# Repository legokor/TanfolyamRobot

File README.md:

# LEGO Kör - TanfolyamRobot

## Fejlesztő környezet

Korábban az STMicroelectronics által biztosított `STM32CubeIDE`-t használtuk a firmware fejlesztéséhez, azonban ez egy elég nehézkes és lassú eszköz. Ezért a tanfolyam során áttérünk egy könnyebben használható és gyorsabb parancssoros toolchain-re, az `STM32CubeCLT`-re. Ezt a toolchain-t a Visual Studio Code nevű (továbbiakban `VSCode`) kód szerkesztővel fogjuk használni, így a teljes fejlesztés (fordítás, feltöltés) nagyon könnyen indítható lesz néhány előre beállított `task`-kal.

## Toolchain

Az előző fejezetben említett módon a firmware fejlesztéséhez az STMicroelectronics parancsoros eszközeit használjuk. Sajnos ezek letöltése regisztrációhoz kötött, ezért feltöltöttük a telepítő fájlokat [a körös drive-ra](https://drive.google.com/drive/folders/1nJ2nfvr9kbIkVAWmcgEXpbxK1OUlX8sQ?usp=sharing), így regisztráció nélkül is telepíteni tudjátok - persze teljesen megértjük, ha nem akartok random drive-os fájlokat telepíteni, viszont ez esetben muszáj regisztrálnotok az [STMicroelectronics weboldalán](https://www.st.com/en/development-tools/stm32cubeclt.html), és onnan letölteni.

Letöltés után a telepítő fájlt futtatva telepítsétek a `STM32CubeCLT`-t egy kényelmes helyre, például `C:\STM32CubeCLT`-be.

**FONTOS:** az `STM32CubeCLT` telepítése után újra kell indítani a `VSCode`-ot amennyiben az már meg volt nyitva, különben a `VSCode` nem fogja látni a telepített toolchain-t. Ezen felül Linux rendszerek esetében előfordulhat, hogy a gépet is újra kell indítani, hogy a megfelelő környezeti változók beálljanak.

Jelenleg Windows 10/11-en és Ubuntu-n teszteljük a szoftvert. Más (Linux alapú) platformokon is valószínűleg működni fog - de ezt nem tudjuk garantálni.

## Robot illesztőszoftver

A robotra a firmware letöltése virtuális soros porton történik, a roboton az USB csatlakozó egy `FT232RL` chiphez kapcsolódik.

Előfordulhat Windows esetében, hogy az nem telepíti automatikusan a virtuális soros port driverét. Erre az esetre a fentebbi drive linken elérhető Windows zip-ben találtok egy plusz driver telepítőt, de amúgy ezt is le tudjátok tölteni az [FTDI weboldaláról](https://ftdichip.com/wp-content/uploads/2021/08/CDM212364_Setup.zip), majd pedig kibontani és telepíteni.

## Kiinduló projekt letöltése, megnyitása

A kiinduló projektet a [GitHub repojából](https://github.com/legokor/TanfolyamRobot) tudjuk letölteni, ehhez az oldal megnyitása után jobb oldalt a `Releases` fül alatt kell kiválasztanunk a **legújabb kiadást**, majd a `tanfrobot.zip` fájlra kell kattintani.

A letöltött fájlt helyezzük el egy kényelmes helyre, például `Documents/Lego_Tanfolyam` mappába, majd bontsuk ki. A kibontás után nyissuk meg a `VSCode`-ot, és a `File -> Open Folder...` menüponttal nyissuk meg a kibontott `firmware` mappát (mely többek közt az `Application`, `Drivers`, `Tools` könyvtárakat tartalmazza).

*Extra tipp:* a `VSCode`-ban érdemes telepíteni az `ms-vscode.cpptools` nevű bővítményt, mely C/C++ nyelv támogatást ad a szerkesztőhöz, így például szintaxis kiemelést és automatikus kiegészítést biztosít.

--------------------------------------------

--------------------------------------------

## *Csak a tanfolyamon kell:* projekt áttekintése, build és upload

Az imént megnyitott projektünk fájljait az IDE bal oldalán láthatjuk. A kód számunkra lényegi része a `tanfolyamrobot/Application/src/app.c` fájl lesz. Itt kell majd megoldanunk a tanfolyam során a feladatokat. Az itt található `app_main()` függvény gombnyomásra indul. Ha ebből a függvényből visszatér a programunk, akkor a robot leáll és a kijelzőn megjeleníti a visszatérési értéket.

A kód fordításához és a robotra való feltöltéséhez a `VSCode`-ban előre beállítottunk néhány `task`-ot, melyeket a `CTRL+SHIFT+B` billentyűkombinációval tudtok elindítani. E billentyűkombináció megnyomása után egy legördülő menüből választhatjátok ki, hogy mit szeretnétek csinálni - számunkra a `CMake Build` és az `STM32 Flash Firmware (FTDI)` lesz a fontos. Előbbi lefordítja a kódot, utóbbi pedig feltölti a robotra. A kiválasztás után egy újabb kérdés fog megjelenni, hogy melyik konfigurációt szeretnénk használni - válasszuk a `Release`-t, majd nyomjunk egy entert.

**FONTOS:** a `CMake Build`-et mindig futtassátok le a `STM32 Flash Firmware (FTDI)` előtt, különben a régi kód fog futni a roboton, nem pedig a legutóbb módosított verzió.

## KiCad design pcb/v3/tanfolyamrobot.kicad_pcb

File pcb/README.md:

# TanfolyamRobot - PCB design considerations

_Note: schematic net and pin names are formatted like_ `this`.

## Microcontroller

The main MCU is an [STM32F103C8T6](https://www.st.com/resource/en/datasheet/stm32f103c8.pdf) in LQFP64 package. There's an option to add an ESP8266 module which communicates with the main MCU via UART.

**The full STM32 pinout and pin assignments can be found in [STM32F103_pin_assignment.xls](STM32F103_pin_assignment.xls)**

### Programming

The STM32 can be programmed using the Serial Wire Debug interface or the integrated Device Firmware Updater. The F103's DFU only supports USART1, so that's connected to an FTDI FT232RL USB-UART converter.

In order to use the DFU, the MCU must be booted in System memory mode by pulling the `BOOT0` pin high at reset.
`BOOT0` is controlled by:
 * the FTDI chip's `RSTN` reset signal, which is high when USB is connected.
 * an FTDI output pin controlled by PC software. The pin can be selected by solder jumpers.

### Reset

Both controllers are connected to the same reset signal, which is a combination of the following reset sources:
 * The reset button
 * Debugger port
 * USB 5V connection
 * an FTDI output pin controlled by PC software. The pin can be selected by solder jumpers.

## Power supply

The battery input connects through a polarity protection MOSFET to the `VCC` rail, which drives the motors and the 5V regulator. Therefore the battery voltage must be at least 5V + the regulator's dropout voltage, and can be as high as the motors' and the motor driver's maximum operating voltage. The polarity protection MOSFET's absolute maximum V<sub>GS</sub> and V<sub>DS</sub> must be higher than the supply voltage.

The `+5V` rail powers the FTDI chip, LCD, ultrasonic sensor, motor encoders, and the servo motor. Therefore the ultrasonic sensor and motor encoder outputs shall be connected to a 5V tolerant MCU pin or level-shifted to 3.3V.

The `+3V3` rail powers the rest of the system: STM32, ESP, color sensor, and it's also the `VCCIO` supply of the FTDI chip.

## Motors

The two motors are driven by a DRV8833 module. For maximum flexibility all of its input ports shall be connected to PWM cabable MCU pins, preferably using the same timer. The driver indicates overcurrent/overheat faults on the `FAULTN` pin, and the whole module can be enabled/disabled by the `SLEEPN` pin.

The STM32's timers have a built-in encoder pulse counter module, which uses the CH1-CH2 channel pair. The motors' encoder pins therefore shall be connected to these timer channels.

The servo output has a 3 pin header with 5V supply and a PWM pin.

## Sensors, LCD

The TCS3200 color sensor has a frequency output. 2 config pins activate the RGB color filters, and 2 config pins set the output frequency scaling. The output pin should be connected to a timer of the MCU. The timer's frequency is not critical as the output full scale frequency can be configured between 12 and 600 kHz.

The generic ultrasonic sensor has a trigger and an echo pin. `ECHO` shall be connected to an interrupt-capable MCU pin.

The character LCD screen operates in 4 bit mode. In this configuration only the `D4`-`D7`, `EN` and `RST` pins are used. Contrast can be set by a trimmer potentiometer on the board. The backlight is also controlled by the MCU, but the control signal is pulled up, so it's on by default.

# MCU connection requirement summary

_I know this looks terrible, but it's my only workaround for GitHub's alternating row colors :disappointed:_

| Component     | Pin/Schematic net      | Type             | MCU requiurement                              |
|---------------|------------------------|------------------|-----------------------------------------------|
| DRV8833       | `IN1`, `IN2`           | PWM/fix input    | 1 PWM, 1 PWM/fix, same timer for all channels |
|||||
|               | `IN3`, `IN4`           | PWM/fix input    | 1 PWM, 1 PWM/fix, same timer for all channels |
|||||
|               | `SLEEPN`               | input            | -                                             |
|||||
|               | `FAULTN`               | output, OC       | -                                             |
|||||
| Encoder       | `ENC1_A`, `ENC1_B`     | output           | Timer CH1 - CH2                               |
|||||
|               | `ENC2_A`, `ENC2_B`     | output           | Timer CH1 - CH2                               |
|||||
| Servo         | `SERVO`                | PWM input        | Timer                                         |
|||||
| TCS3200       | `S0`-`S3`              | input            | -                                             |
|||||
|               | `OUT`                  | frequency output | Timer                                         |
|||||
| Generic US    | `TRIG`                 | input            | -                                             |
|||||
|               | `ECHO`                 | output           | Interrupt                                     |
|||||
| LCD           | `RST`,`EN`, `D4`-`D7`  | input            | -                                             |
|||||
|               | `BACKLIGHT`            | input            | Preferably PWM                                |
|||||
| ESP8266       | `RX`, `TX`             | UART             | Any UART                                      |
|||||
| SWD connector | `SWCLK`, `SWDIO`, `SWO`| Debug            | Corresponding debugger pins                   |
|||||
| FT232RL       | `RX`, `TX`             | UART             | UART1                                         |

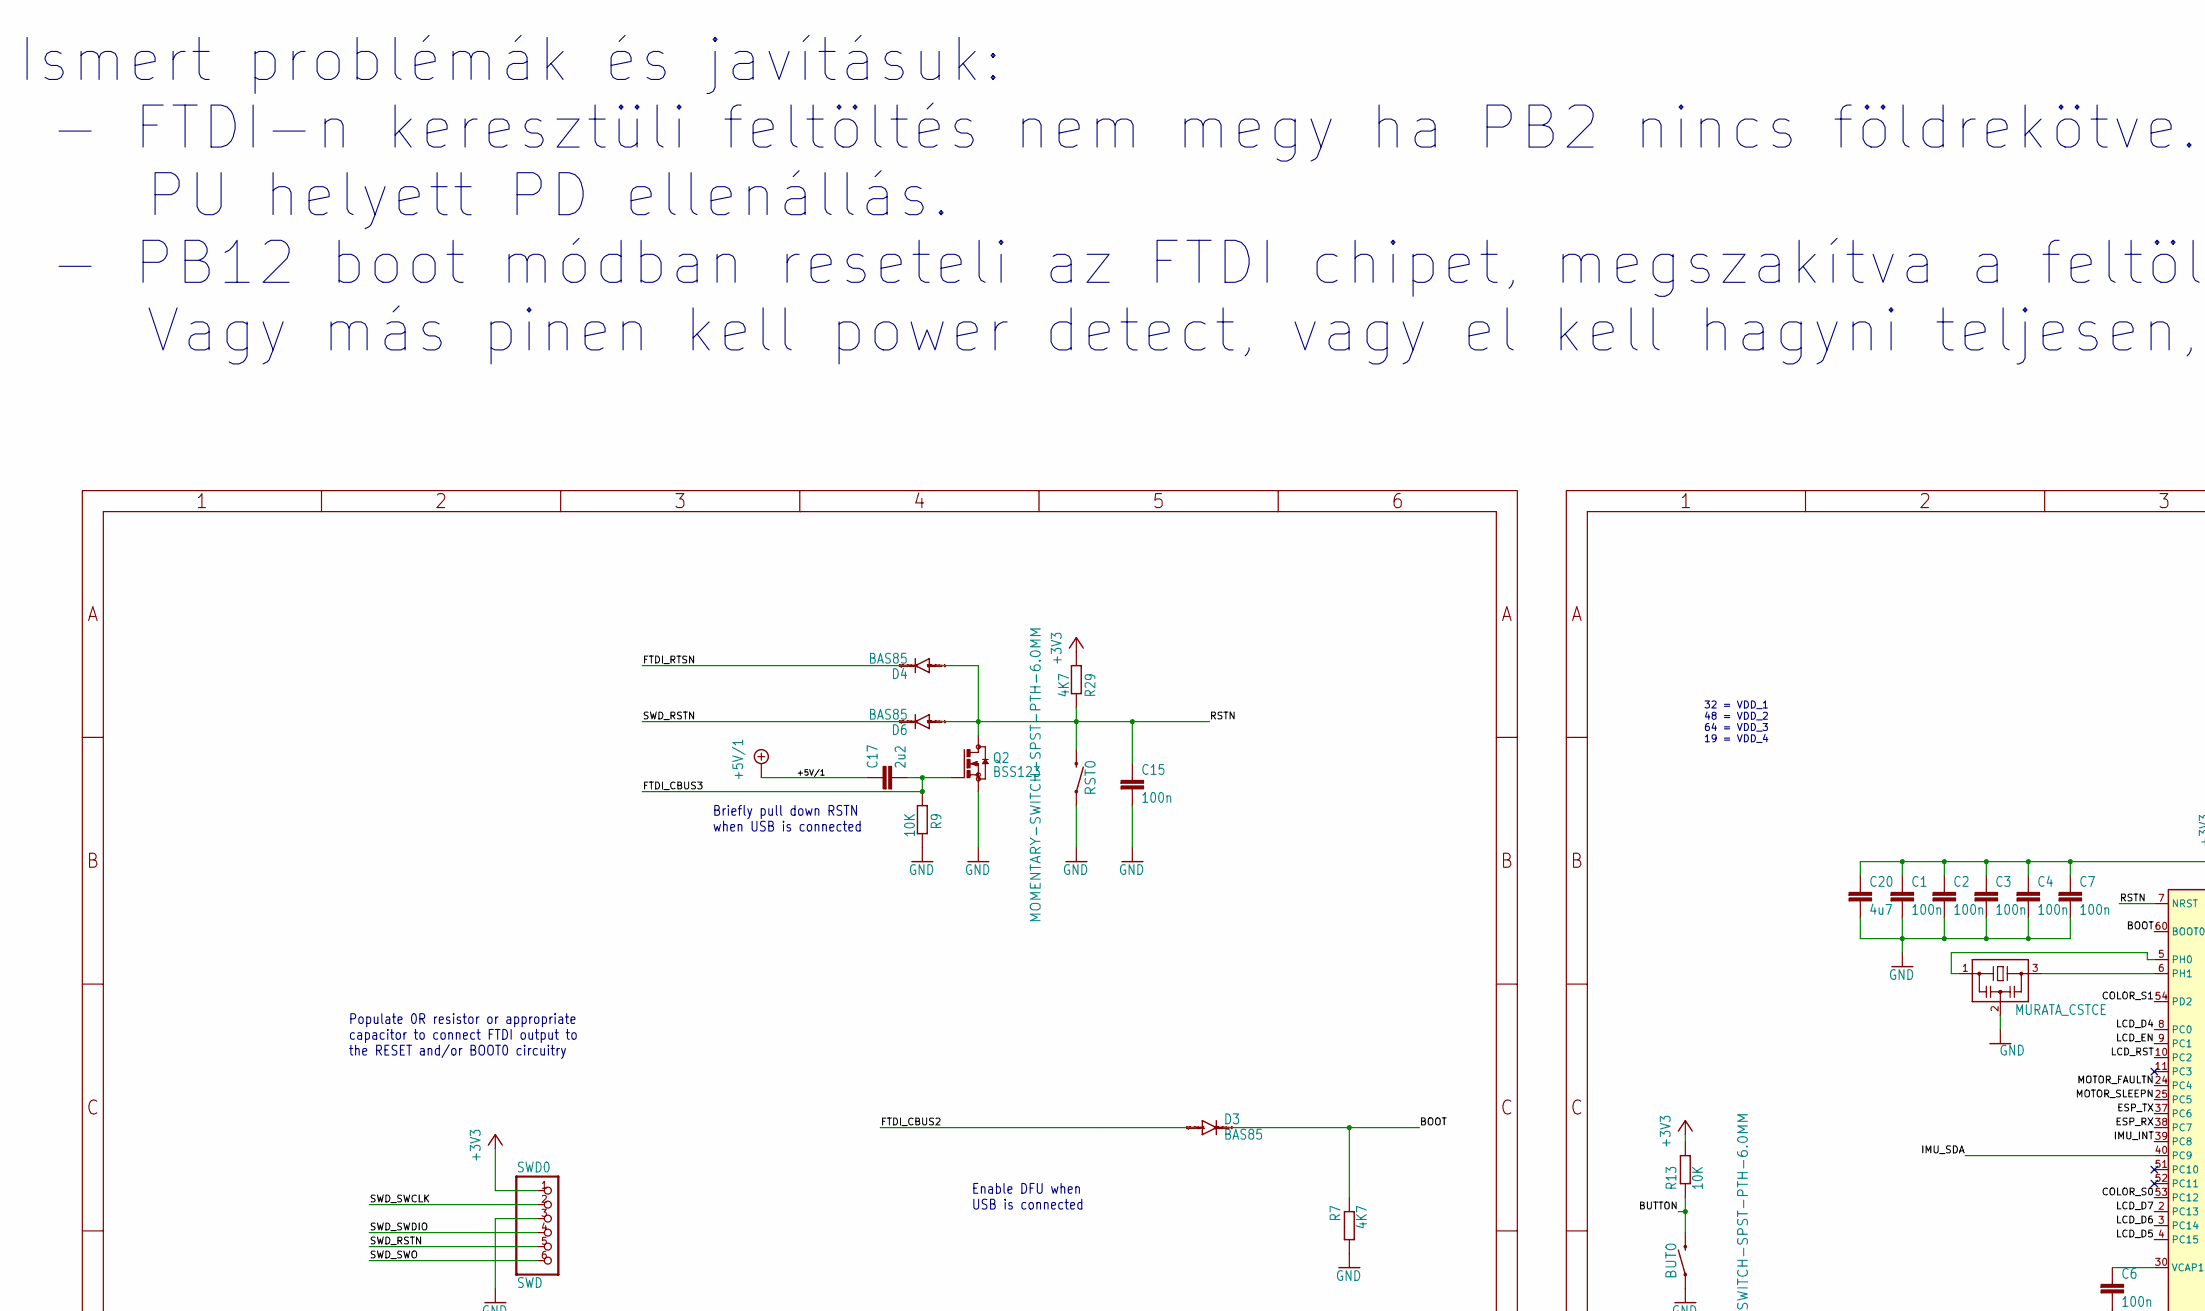
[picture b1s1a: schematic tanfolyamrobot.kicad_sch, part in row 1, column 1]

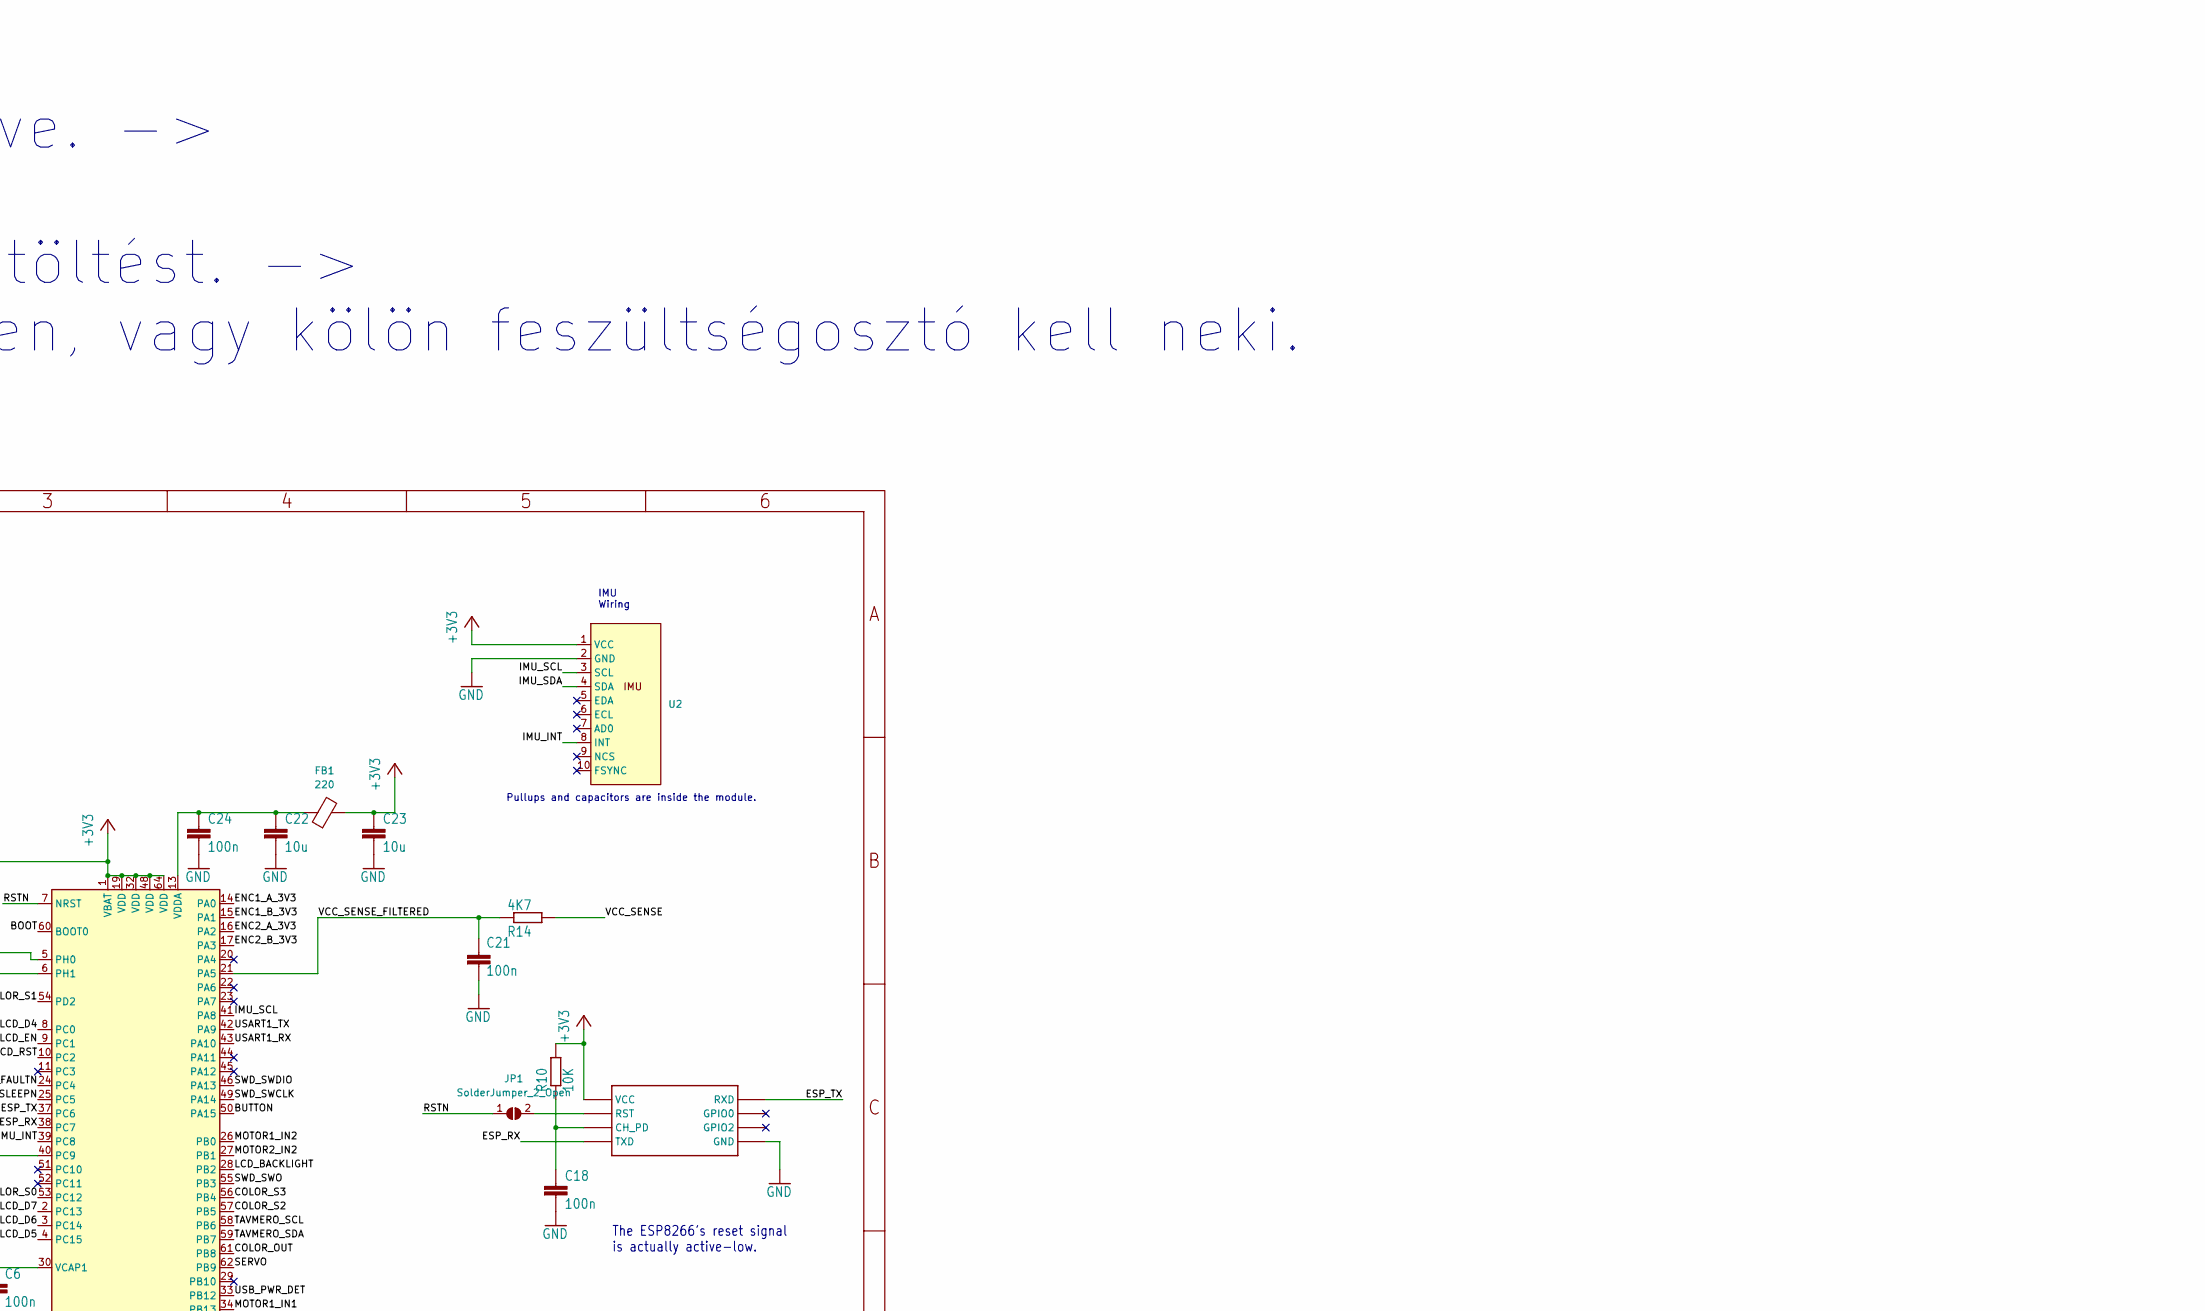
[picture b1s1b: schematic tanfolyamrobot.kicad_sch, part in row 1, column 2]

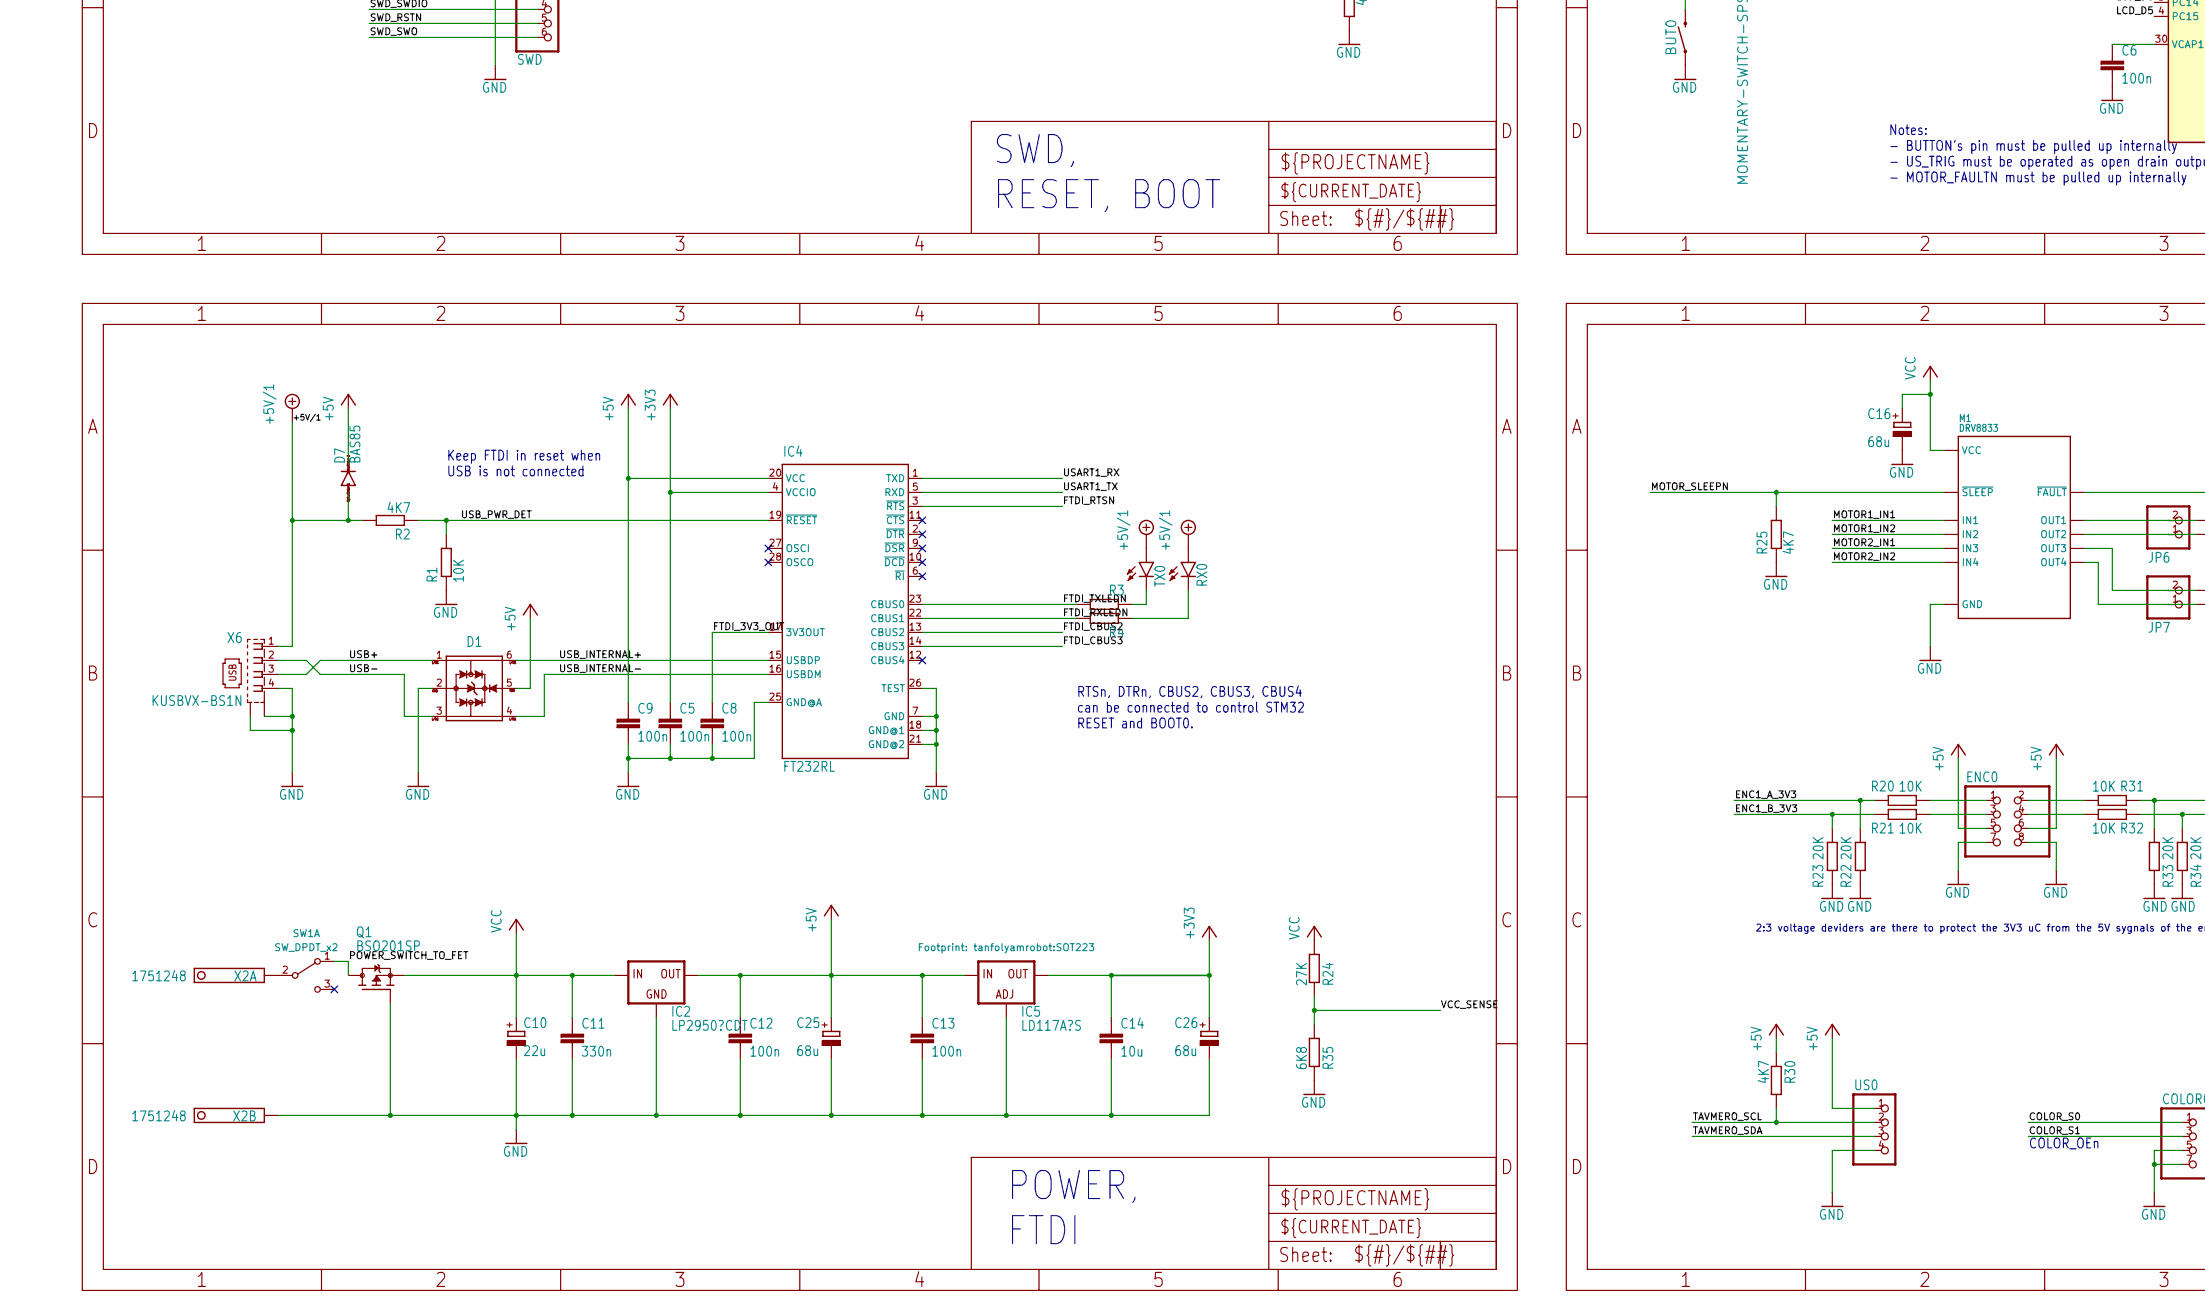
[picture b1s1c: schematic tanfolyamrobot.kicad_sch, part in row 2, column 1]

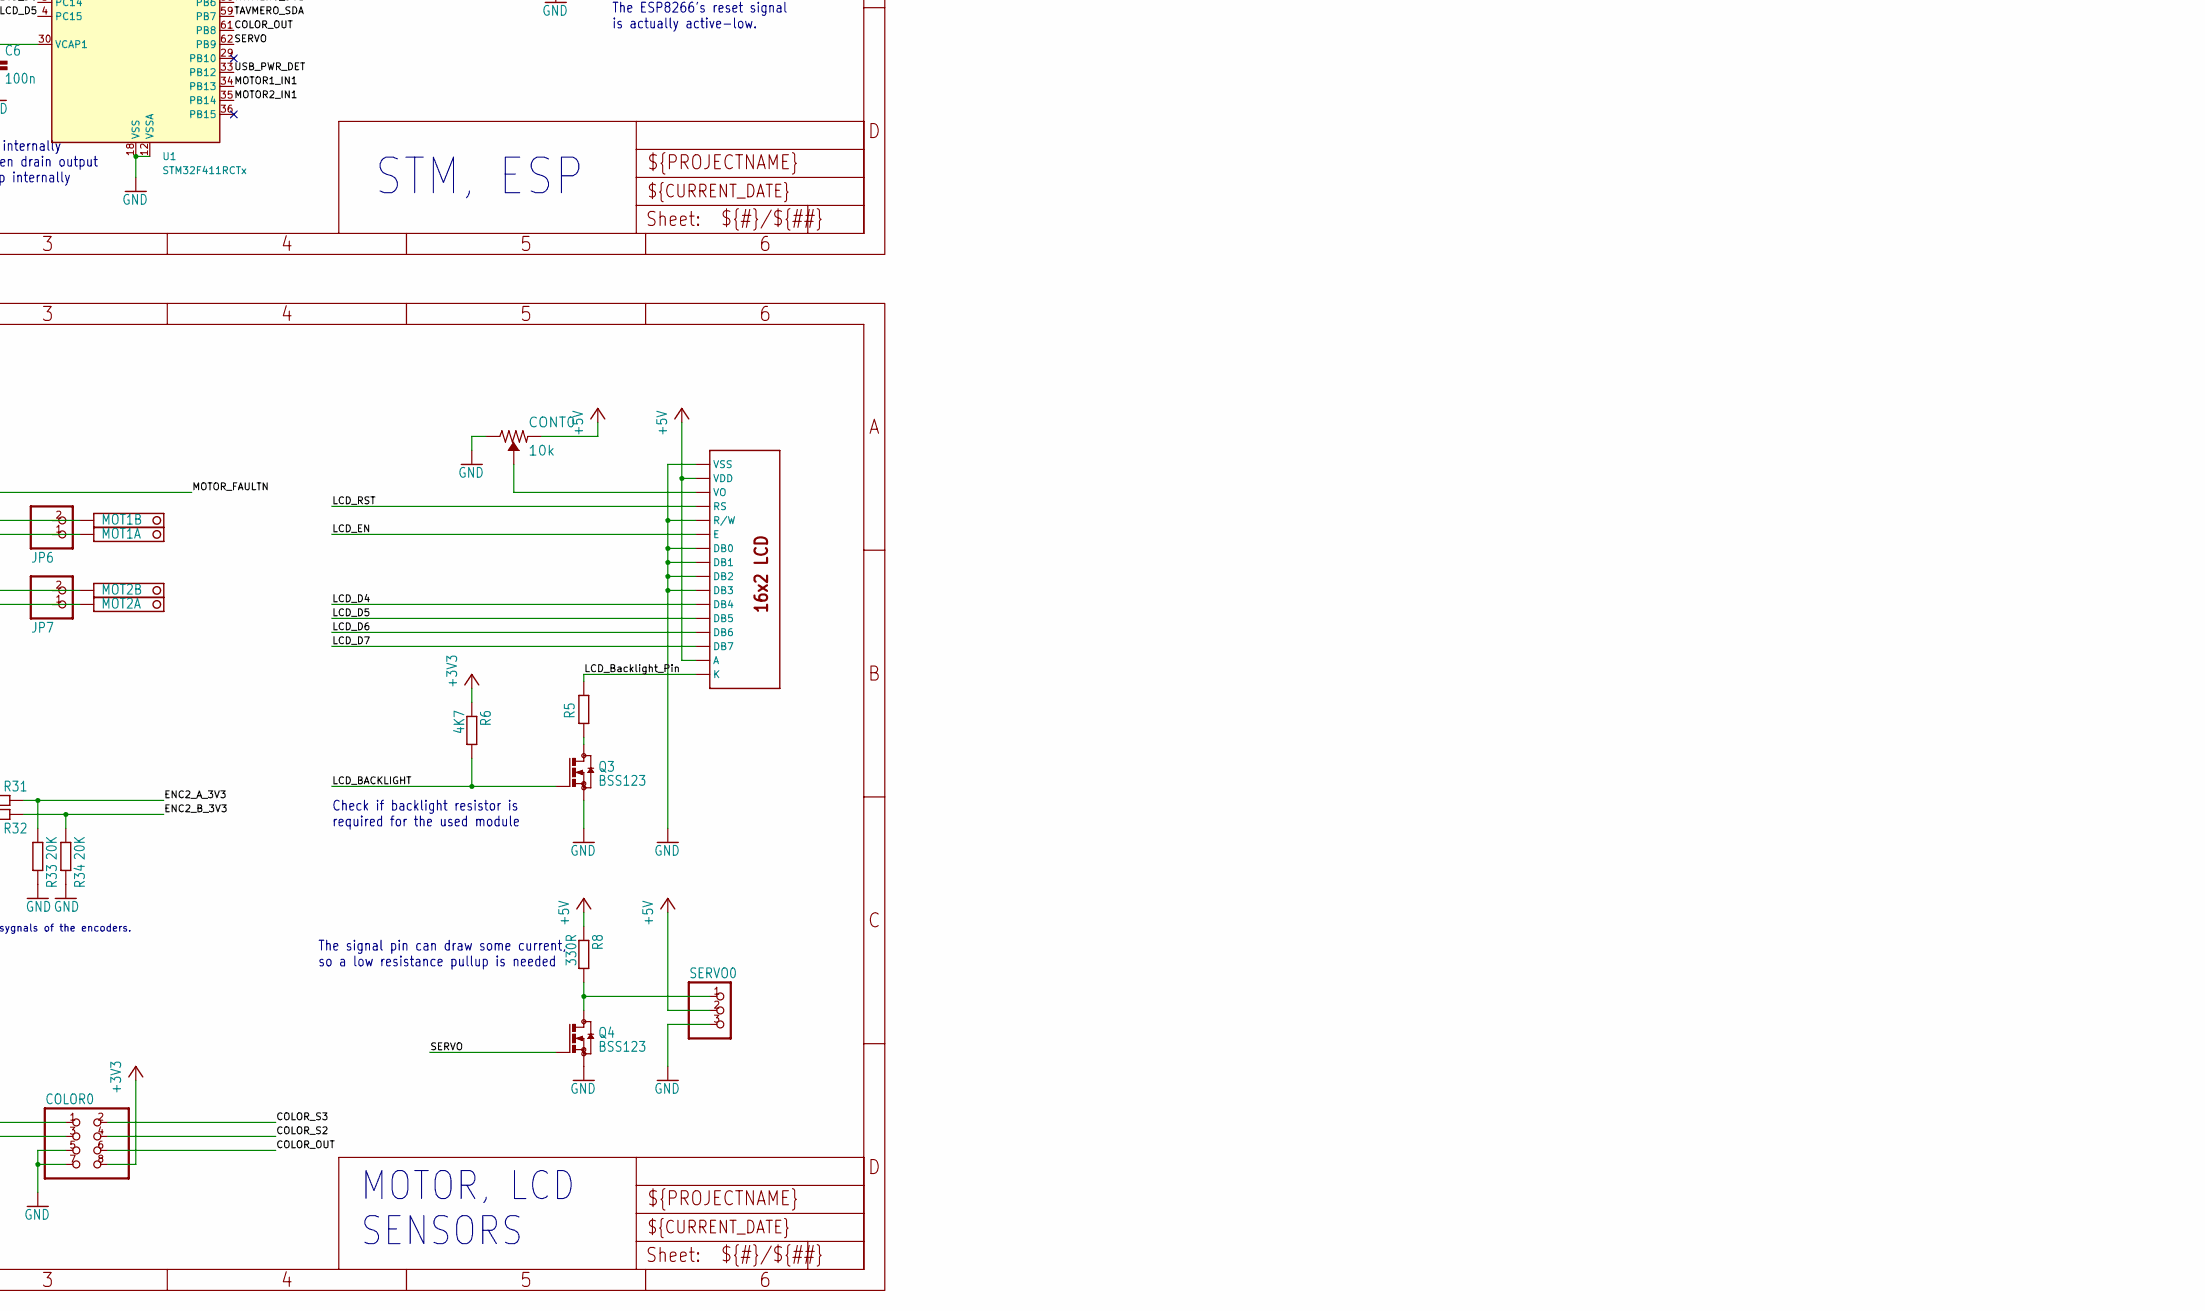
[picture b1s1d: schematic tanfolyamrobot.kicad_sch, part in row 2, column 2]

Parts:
BUT0: MOMENTARY-SWITCH-SPST-PTH-6.0MM; TACTILE_SWITCH_PTH_6.0MM
C1, C2, C3, C4, C5, C6, C7, C8, C9, C15, C18, C21, C24: 100n; C0603
C10: 22u; B_3528-21R
C11: 330n; C0805K
C12, C13: 100n; C0805K
C14, C22, C23: 10u; C0805K
C16, C25, C26: 68u; B_3528-21R
C17: 2u2; C0603
C20: 4u7; C0603
COLOR0: PINHD-2X4/90; 2X04_90
CONT0: 10k; TRIMPOT-SMD-3MM-CLOSED
D1: WE-TVS-HS_SOT23-6L_82400102; WE-TVS_SOT23-6L
D3, D4, D6: BAS85; D_SOD-323F
D7: BAS85; DO-214AC
ENC0: PINHD-2X4/90; 2X04_90
FB1: 220; L_0603_1608Metric
IC2: LP2950?CDT; DPACK
IC4: FT232RL; SSOP28
IC5: LD117A?S; SOT223
JP1: SolderJumper_2_Open; SolderJumper-2_P1.3mm_Open_Pad1.0x1.5mm
JP6, JP7: PINHD-1X2; 1X02
LCD1: LCD-16X2NOSILK; LCD-16X2_NOSILK
M1: DRV8833; DRV8833_MODULE
MOT1, MOT2: 1751248
Q1: BSO201SP; SO-8
Q2, Q3, Q4: BSS123; SOT23
R1, R9, R10, R13, R20, R21, R31, R32: 10K; R0603
R2, R6, R7, R14, R25, R29, R30: 4K7; R0603
R3, R4, R5: R-EU_R0603; R0603
R8: 330R; R0603
R22, R23, R33, R34: 20K; R0603
R24: 27K; R0603
R35: 6K8; R0603
RST0: MOMENTARY-SWITCH-SPST-PTH-6.0MM; TACTILE_SWITCH_PTH_6.0MM
RX0: LEDCHIP-LED0603; LED_0603_1608Metric
SERVO0: PINHD-1X3/90; 1X03_90
SW1: SW_DPDT_x2; SW_E-Switch_EG1271_SPDT
SWD0: SWD; 1X06
TX0: LEDCHIP-LED0603; LED_0603_1608Metric
U1: STM32F411RCTx; LQFP-64_10x10mm_P0.5mm
U2: PCB_IMU
U$1: ESP01
US0: PINHD-1X4/90; 1X04_90
X1: MURATA_CSTCE; CSTCE
X2: 1751248
X6: KUSBVX-BS1N

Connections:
+3V3: C1.1, C2.1, C3.1, C4.1, C5.1, C7.1, C14.1, C20.1, C23.1, C26.+, COLOR0.8, FB1.2, IC4.4 (VCCIO), IC5.4 (OUT), R6.1, R10.2, R13.2, R29.1, SWD0.1, U1.1 (VBAT), U1.19 (VDD), U1.32 (VDD), U1.48 (VDD), U1.64 (VDD), U2.1 (VCC), U$1.VCC
+5V: C9.1, C12.1, C13.1, C25.+, CONT0.1 (CCW), D1.5 (VDD), D7.C, ENC0.5, ENC0.6, IC2.3 (OUT), IC4.20 (VCC), IC5.3 (IN), LCD1.2 (VDD), LCD1.15 (A), R8.1, R30.1, SERVO0.2, US0.1
+5V/1: C17.1, D7.A, R2.2, RX0.2, TX0.2, X6.1
/BOOT: D3.1, R7.1, U1.60 (BOOT0)
/BUTTON: BUT0.3 (2), R13.1, U1.50 (PA15)
/COLOR_OUT: COLOR0.6, U1.61 (PB8)
/COLOR_S0: COLOR0.1, U1.53 (PC12)
/COLOR_S1: COLOR0.3, U1.54 (PD2)
/COLOR_S2: COLOR0.4, U1.57 (PB5)
/COLOR_S3: COLOR0.2, U1.56 (PB4)
/ENC1_A_3V3: R20.2, R22.1, U1.14 (PA0)
/ENC1_B_3V3: R21.2, R23.1, U1.15 (PA1)
/ENC2_A_3V3: R31.2, R33.1, U1.16 (PA2)
/ENC2_B_3V3: R32.2, R34.1, U1.17 (PA3)
/ESP_RX: U1.38 (PC7), U$1.TX (TXD)
/ESP_TX: U1.37 (PC6), U$1.RX (RXD)
/FTDI_3V3_OUT: C8.1, IC4.17 (3V3OUT)
/FTDI_CBUS2: D3.2, IC4.13 (CBUS2)
/FTDI_CBUS3: C17.2, IC4.14 (CBUS3), Q2.1 (G), R9.1
/FTDI_RTSN: D4.1, IC4.3 (~RTS)
/FTDI_RXLEDN: IC4.22 (CBUS1), R4.2
/FTDI_TXLEDN: IC4.23 (CBUS0), R3.2
/IMU_INT: U1.39 (PC8), U2.8 (INT)
/IMU_SCL: U1.41 (PA8), U2.3 (SCL)
/IMU_SDA: U1.40 (PC9), U2.4 (SDA)
/LCD_BACKLIGHT: Q3.1 (G), R6.2, U1.28 (PB2)
/LCD_Backlight_Pin: LCD1.16 (K), R5.2
/LCD_D4: LCD1.11 (DB4), U1.8 (PC0)
/LCD_D5: LCD1.12 (DB5), U1.4 (PC15)
/LCD_D6: LCD1.13 (DB6), U1.3 (PC14)
/LCD_D7: LCD1.14 (DB7), U1.2 (PC13)
/LCD_EN: LCD1.6 (E), U1.9 (PC1)
/LCD_RST: LCD1.4 (RS), U1.10 (PC2)
/MOTOR1_IN1: M1.IN1, U1.34 (PB13)
/MOTOR1_IN2: M1.IN2, U1.26 (PB0)
/MOTOR2_IN1: M1.IN3, U1.35 (PB14)
/MOTOR2_IN2: M1.IN4, U1.27 (PB1)
/MOTOR_FAULTN: M1.!FAULT (~FAULT), U1.24 (PC4)
/MOTOR_SLEEPN: M1.!SLEEP (~SLEEP), R25.2, U1.25 (PC5)
/POWER_SWITCH_TO_FET: Q1.5 (D), Q1.6 (D), Q1.7 (D), Q1.8 (D), SW1.1 (A)
/RSTN: C15.1, D4.2, D6.2, JP1.1 (A), Q2.3 (D), R29.2, RST0.3 (2), U1.7 (NRST)
/SERVO: Q4.1 (G), U1.62 (PB9)
/SWD_RSTN: D6.1, SWD0.5
/SWD_SWCLK: SWD0.2, U1.49 (PA14)
/SWD_SWDIO: SWD0.4, U1.46 (PA13)
/SWD_SWO: SWD0.6, U1.55 (PB3)
/TAVMERO_SCL: R30.2, U1.58 (PB6), US0.2
/TAVMERO_SDA: U1.59 (PB7), US0.3
/USART1_RX: IC4.1 (TXD), U1.43 (PA10)
/USART1_TX: IC4.5 (RXD), U1.42 (PA9)
/USB+: D1.1 (I/O1), X6.3
/USB-: D1.3 (I/O2), X6.2
/USB_INTERNAL+: D1.6 (I/O3), IC4.15 (USBDP)
/USB_INTERNAL-: D1.4 (I/O4), IC4.16 (USBDM)
/USB_PWR_DET: IC4.19 (~RESET), R1.2, R2.1, U1.33 (PB12)
/VCC_SENSE: R14.2, R24.2, R35.1
/VCC_SENSE_FILTERED: C21.1, R14.1, U1.21 (PA5)
GND: BUT0.1, C1.2, C2.2, C3.2, C4.2, C5.2, C6.2, C7.2, C8.2, C9.2, C10.-, C11.2, C12.2, C13.2, C14.2, C15.2, C16.-, C18.2, C20.2, C21.2, C22.2, C23.2, C24.2, C25.-, C26.-, COLOR0.5, COLOR0.7, CONT0.3 (CW), D1.2 (GND), ENC0.7, ENC0.8, IC2.4 (GND), IC4.7 (GND), IC4.18 (GND@1), IC4.21 (GND@2), IC4.25 (GND@A), IC4.26 (TEST), IC5.1 (ADJ), LCD1.1 (VSS), LCD1.5 (R/W), LCD1.7 (DB0), LCD1.8 (DB1), LCD1.9 (DB2), LCD1.10 (DB3), M1.GND, Q1.4 (G), Q2.2 (S), Q3.2 (S), Q4.2 (S), R1.1, R7.2, R9.2, R22.2, R23.2, R25.1, R33.2, R34.2, R35.2, RST0.1, SERVO0.3, SWD0.3, U1.12 (VSSA), U1.18 (VSS), U1.31 (VSS), U1.47 (VSS), U1.63 (VSS), U2.2 (GND), U$1.GND, US0.4, X1.2, X2.2 (K), X6.4, X6.M1 (S1), X6.M2 (S2)
unnamed: C18.1, R10.1, U$1.CH_PD
unnamed: CONT0.2 (WIPER), LCD1.3 (VO)
unnamed: ENC0.1, R20.1
unnamed: ENC0.2, R31.1
unnamed: ENC0.3, R21.1
unnamed: ENC0.4, R32.1
unnamed: JP1.2 (B), U$1.RST
unnamed: JP6.1, M1.OUT2, MOT1.1 (K)
unnamed: JP6.2, M1.OUT1, MOT1.2 (K)
unnamed: JP7.1, M1.OUT4, MOT2.1 (K)
unnamed: JP7.2, M1.OUT3, MOT2.2 (K)
unnamed: Q3.3 (D), R5.1
unnamed: Q4.3 (D), R8.2, SERVO0.1
unnamed: R3.1, TX0.1
unnamed: R4.1, RX0.1
unnamed: SW1.2 (B), X2.1 (K)
unnamed: U1.5 (PH0), X1.1
unnamed: U1.6 (PH1), X1.3
unnamed: C6.1, U1.30 (VCAP1)
unnamed: C22.1, C24.1, FB1.1, U1.13 (VDDA)
VCC: C10.+, C11.1, C16.+, IC2.1 (IN), M1.VCC, Q1.1 (S), Q1.2 (S), Q1.3 (S), R24.1

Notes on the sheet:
MOTOR, LCD SENSORS
Check if backlight resistor is required for the used module
IMU Wiring
Enable DFU when USB is connected
POWER, FTDI
Briefly pull down RSTN when USB is connected
32 = VDD_1 48 = VDD_2 64 = VDD_3 19 = VDD_4
Keep FTDI in reset when USB is not connected
COLOR_OEn
Ismert problémák és javításuk: - FTDI-n keresztüli feltöltés nem megy ha PB2 nincs földrekötve. -> PU helyett PD ellenállás. - PB12 boot módban reseteli az FTDI chipet, megszakítva a feltöltést. -> Vagy más pinen kell power detect, vagy el kell hagyni teljesen, vagy kölön feszültségosztó kell neki.
Notes: - BUTTON's pin must be pulled up internally - US_TRIG must be operated as open drain output - MOTOR_FAULTN must be pulled up internally
RTSn, DTRn, CBUS2, CBUS3, CBUS4 can be connected to control STM32 RESET and BOOT0.
Pullups and capacitors are inside the module.
STM, ESP
SWD, RESET, BOOT
The signal pin can draw some current, so a low resistance pullup is needed
Populate 0R resistor or appropriate capacitor to connect FTDI output to the RESET and/or BOOT0 circuitry
The ESP8266's reset signal is actually active-low.
2:3 voltage deviders are there to protect the 3V3 uC from the 5V sygnals of the encoders.

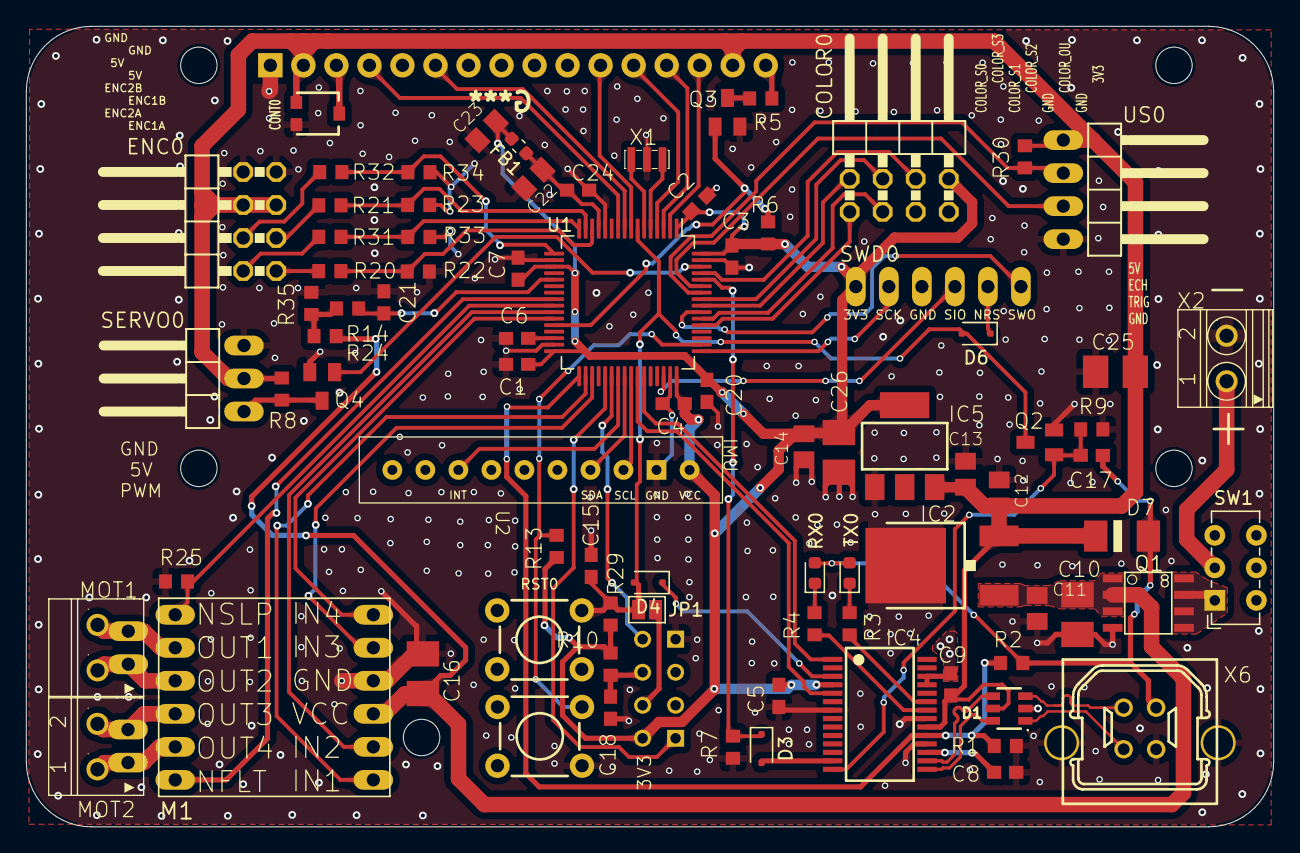
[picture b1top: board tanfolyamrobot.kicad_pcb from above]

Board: 2 copper layers, 95.9 x 61.6 mm, 87 parts (0 on the bottom side), 79 nets.

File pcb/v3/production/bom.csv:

Designator,Footprint,Quantity,Value,LCSC Part #
,,1,,
"BUT0, RST0",TACTILE_SWITCH_PTH_6.0MM,2,MOMENTARY-SWITCH-SPST-PTH-6.0MM,
"C1, C15, C18, C2, C21, C24, C3, C4, C5, C6, C7, C8, C9",C0603,13,100n,
C10,B_3528-21R,1,22u,
C11,C0805K,1,330n,
"C12, C13",C0805K,2,100n,
"C14, C22, C23",C0805K,3,10u,
"C16, C25, C26",B_3528-21R,3,68u,
C17,C0603,1,2u2,
C20,C0603,1,4u7,
"COLOR0, ENC0",2X04_90,2,PINHD-2X4/90,
CONT0,TRIMPOT-SMD-3MM-CLOSED,1,10k,
D1,WE-TVS_SOT23-6L,1,WE-TVS-HS_SOT23-6L_82400102,
"D3, D4, D6",D_SOD-323F,3,BAS85,
D7,DO-214AC,1,BAS85,
FB1,0603,1,220,
IC2,DPACK,1,LP2950?CDT,
IC4,SSOP28,1,FT232RL,
IC5,SOT223,1,LD117A?S,
JP1,SolderJumper-2_P1.3mm_Open_Pad1.0x1.5mm,1,SolderJumper_2_Open,
"JP6, JP7",1X02,2,PINHD-1X2,
LCD1,LCD-16X2_NOSILK,1,LCD-16X2NOSILK,
M1,DRV8833_MODULE,1,DRV8833,
"MOT1, MOT2, X2",1751248,3,1751248,
Q1,SO-8,1,BSO201SP,
"Q2, Q3, Q4",SOT23,3,BSS123,
"R1, R10, R13, R20, R21, R31, R32, R9",R0603,8,10K,
"R14, R2, R25, R29, R30, R6, R7",R0603,7,4K7,
"R22, R23, R33, R34",R0603,4,20K,
R24,R0603,1,27K,
"R3, R4, R5",R0603,3,R-EU_R0603,
R35,R0603,1,6K8,
R8,R0603,1,330R,
"RX0, TX0",0603,2,LEDCHIP-LED0603,
SERVO0,1X03_90,1,PINHD-1X3/90,
SW1,SW_E-Switch_EG1271_SPDT,1,SW_DPDT_x2,
SWD0,1X06,1,SWD,
U$1,ESP01,1,ESP01,
U1,LQFP-64_10x10mm_P0.5mm,1,STM32F411RCTx,
U2,PCB_IMU,1,~,
US0,1X04_90,1,PINHD-1X4/90,
X1,CSTCE,1,MURATA_CSTCE,
X6,KUSBVX-BS1N,1,KUSBVX-BS1N,

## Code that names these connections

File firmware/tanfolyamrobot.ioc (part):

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Mcu.Name=STM32F103R(8-B)Tx
Mcu.Package=LQFP64
Mcu.UserName=STM32F103R8Tx
PA0-WKUP.GPIOParameters=GPIO_Label,GPIO_ModeDefaultEXTI
PA0-WKUP.GPIO_Label=ENC1_A
PA0-WKUP.GPIO_ModeDefaultEXTI=GPIO_MODE_IT_RISING
PA0-WKUP.Signal=GPXTI0
PA1.GPIOParameters=GPIO_Label
PA1.GPIO_Label=ENC1_B
PA1.Signal=GPIO_Input
PA10.Mode=Asynchronous
PA10.Signal=USART1_RX
PA13.Mode=Trace_Asynchronous_SW
PA13.Signal=SYS_JTMS-SWDIO
PA14.Mode=Trace_Asynchronous_SW
PA14.Signal=SYS_JTCK-SWCLK
PA15.GPIOParameters=GPIO_PuPd,GPIO_Label
PA15.GPIO_Label=BUTTON
PA15.GPIO_PuPd=GPIO_PULLUP
PA15.Signal=GPIO_Input
PA2.GPIOParameters=GPIO_Label
PA2.GPIO_Label=SERVO
PA2.Signal=S_TIM2_CH3
PA5.GPIOParameters=GPIO_Label
PA5.GPIO_Label=VCC_SENSE
PA5.Signal=ADCx_IN5
PA6.GPIOParameters=GPIO_Label,GPIO_ModeDefaultEXTI
PA6.GPIO_Label=ENC2_A
PA6.GPIO_ModeDefaultEXTI=GPIO_MODE_IT_RISING
PA6.Signal=GPXTI6
PA7.GPIOParameters=GPIO_Label
PA7.GPIO_Label=ENC2_B
PA7.Signal=GPIO_Input
PA9.Mode=Asynchronous
PA9.Signal=USART1_TX
PB0.GPIOParameters=GPIO_Label
PB0.GPIO_Label=MOTOR1_PWM2
PB0.Signal=S_TIM3_CH3
PB1.GPIOParameters=GPIO_Label
PB1.GPIO_Label=MOTOR2_PWM2
PB1.Signal=S_TIM3_CH4
PB10.GPIOParameters=GPIO_Label,GPIO_Pu
PB10.GPIO_Label=IMU_SCL
PB10.GPIO_Pu=GPIO_PULLUP
PB10.Mode=I2C
PB10.Signal=I2C2_SCL
PB11.GPIOParameters=GPIO_Label,GPIO_Pu
PB11.GPIO_Label=IMU_SDA
PB11.GPIO_Pu=GPIO_PULLUP
PB11.Mode=I2C
PB11.Signal=I2C2_SDA
PB12.GPIOParameters=GPIO_PuPd,GPIO_Label
PB12.GPIO_Label=USB_PWR_DET
PB12.GPIO_PuPd=GPIO_PULLDOWN
PB12.Signal=GPIO_Input
PB13.GPIOParameters=GPIO_Label
PB13.GPIO_Label=MOTOR1_PWM1
PB13.Mode=PWM Generation1 CH1N
PB13.Signal=TIM1_CH1N
PB14.GPIOParameters=GPIO_Label
PB14.GPIO_Label=MOTOR2_PWM1
PB14.Mode=PWM Generation2 CH2N
PB14.Signal=TIM1_CH2N
PB3.Mode=Trace_Asynchronous_SW
PB3.Signal=SYS_JTDO-TRACESWO
PB4.GPIOParameters=GPIO_Label
PB4.GPIO_Label=COLOR_S3
PB4.Signal=GPIO_Output
PB5.GPIOParameters=GPIO_Label
PB5.GPIO_Label=COLOR_S2
PB5.Signal=GPIO_Output
PB6.GPIOParameters=GPIO_Label
PB6.GPIO_Label=TIM4_CH1_US_ECHO
PB6.Signal=S_TIM4_CH1
PB7.GPIOParameters=GPIO_Label,GPIO_ModeDefaultOutputPP
PB7.GPIO_Label=US_TRIG
PB7.GPIO_ModeDefaultOutputPP=GPIO_MODE_OUTPUT_OD
PB7.Signal=GPIO_Output
PB8.GPIOParameters=GPIO_Label
PB8.GPIO_Label=TIM4_CH3_COLOR
PB8.Signal=S_TIM4_CH3
PB9.GPIOParameters=PinState,GPIO_Label
PB9.GPIO_Label=LCD_BACKLIGHT
PB9.PinState=GPIO_PIN_RESET
PB9.Signal=GPIO_Output
PC0.GPIOParameters=GPIO_Label
PC0.GPIO_Label=LCD_D4
PC0.Signal=GPIO_Output
PC1.GPIOParameters=GPIO_Label
PC1.GPIO_Label=LCD_EN
PC1.Signal=GPIO_Output
PC10.Mode=Asynchronous
PC10.Signal=USART3_TX
PC11.Mode=Asynchronous
PC11.Signal=USART3_RX
PC12.GPIOParameters=GPIO_Label
PC12.GPIO_Label=COLOR_S0
PC12.Signal=GPIO_Output
PC13-TAMPER-RTC.GPIOParameters=GPIO_Label
PC13-TAMPER-RTC.GPIO_Label=LCD_D7
PC13-TAMPER-RTC.Signal=GPIO_Output
PC14-OSC32_IN.GPIOParameters=GPIO_Label
PC14-OSC32_IN.GPIO_Label=LCD_D6
PC14-OSC32_IN.Signal=GPIO_Output
PC15-OSC32_OUT.GPIOParameters=GPIO_Label
PC15-OSC32_OUT.GPIO_Label=LCD_D5
PC15-OSC32_OUT.Signal=GPIO_Output
PC2.GPIOParameters=GPIO_Label
PC2.GPIO_Label=LCD_RST
PC2.Signal=GPIO_Output
PC4.GPIOParameters=GPIO_PuPd,GPIO_Label
PC4.GPIO_Label=MOTOR_FAULTN
PC4.GPIO_PuPd=GPIO_PULLUP
PC4.Signal=GPIO_Input
PC5.GPIOParameters=PinState,GPIO_Label
PC5.GPIO_Label=MOTOR_SLEEPN
PC5.PinState=GPIO_PIN_RESET
PC5.Signal=GPIO_Output
PD0-OSC_IN.Mode=HSE-External-Oscillator
PD0-OSC_IN.Signal=RCC_OSC_IN
PD1-OSC_OUT.Mode=HSE-External-Oscillator
PD1-OSC_OUT.Signal=RCC_OSC_OUT
PD2.GPIOParameters=GPIO_Label
PD2.GPIO_Label=COLOR_S1
PD2.Signal=GPIO_Output
RCC.SYSCLKFreq_VALUE=72000000
RCC.SYSCLKSource=RCC_SYSCLKSOURCE_PLLCLK
board=custom
